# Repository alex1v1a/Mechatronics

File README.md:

# Mechatronics
Progress of Mechatronics 282 778

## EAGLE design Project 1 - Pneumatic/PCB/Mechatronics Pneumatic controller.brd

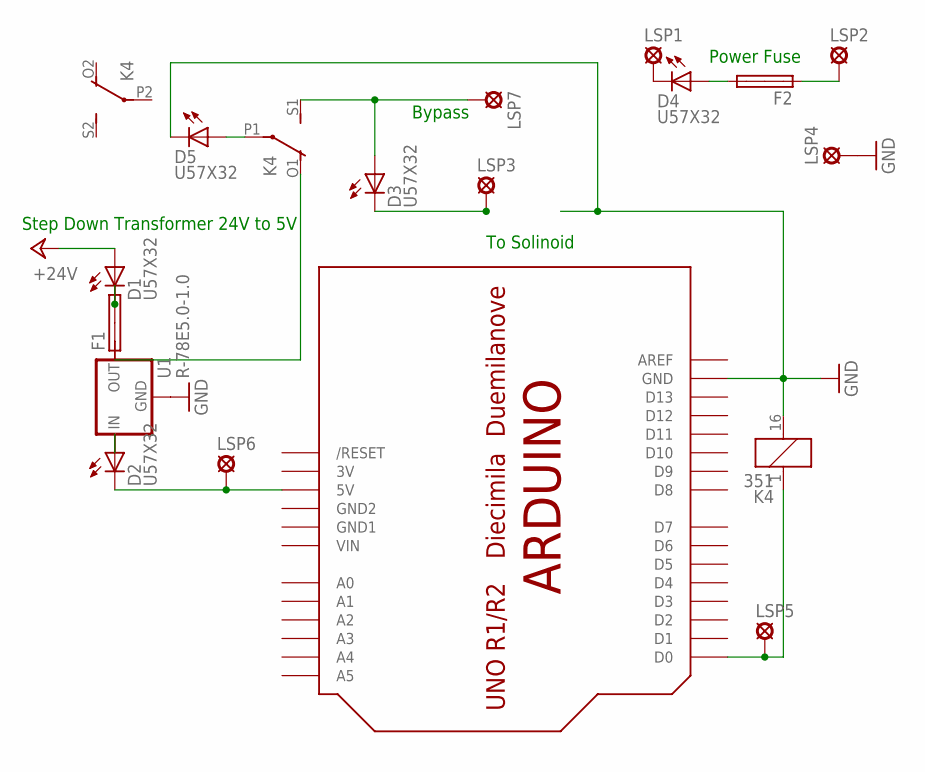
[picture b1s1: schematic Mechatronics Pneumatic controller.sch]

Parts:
D1, D2, D3, D4, D5: U57X32
F1, F2: SHK20L
K4: 351
LSP1, LSP2, LSP3, LSP4, LSP5, LSP6, LSP7: LSP10
U1: R-78E5.0-1.0; DC-DC_CONVERTER_78XX
U$1: ARDUINOUNO; ARDUINO

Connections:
3V: U$1.3V
5VSOURCE: D2.K (C), LSP6.MP, U$1.5V
+24V: D1.A
GND: D5.K (C), K4.16 (2), LSP4.MP, U1.GND, U$1.GND
GND1: U$1.GND1
GND2: U$1.GND2
unnamed: D1.K (C), F1.2A, F1.2B
unnamed: F1.1B, U1.VOUT (OUT)
unnamed: D2.A, U1.VIN (IN)
unnamed: K4.1, LSP5.MP, U$1.D0
unnamed: D3.A, K4.S1 (S), LSP7.MP
unnamed: D3.K (C), LSP3.MP
unnamed: D4.A, F2.2A
unnamed: F2.1A, LSP2.MP
unnamed: D4.K (C), LSP1.MP
unnamed: D5.A, K4.P1
SOLINOID: F1.1A, K4.O1 (O)
VIN: U$1.VIN

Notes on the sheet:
Step Down Transformer 24V to 5V
To Solinoid
Power Fuse
Bypass

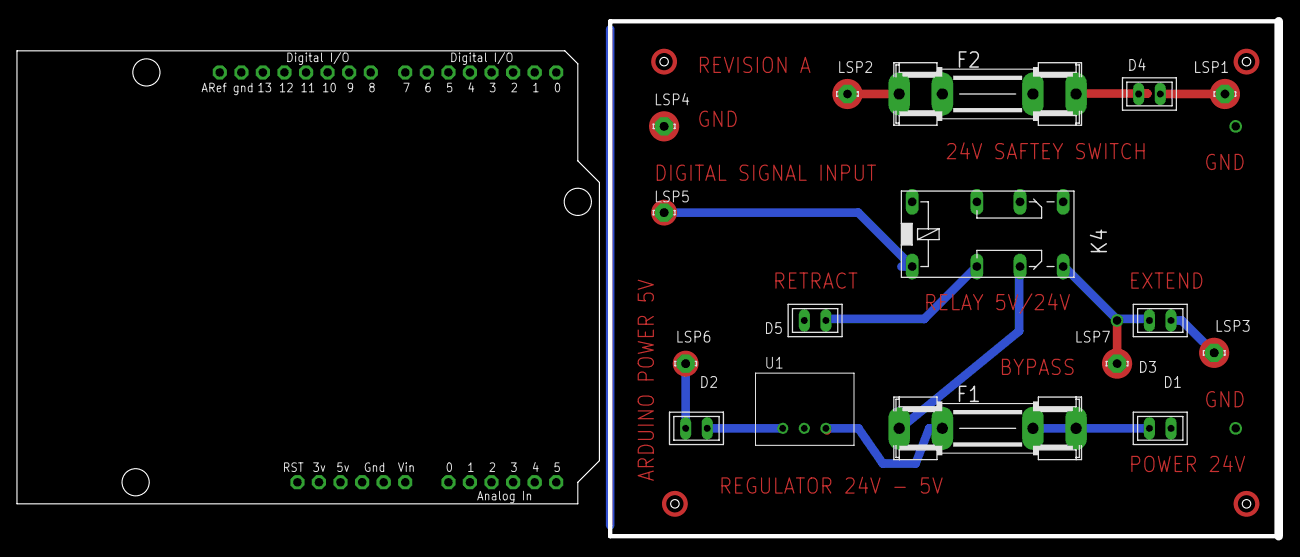
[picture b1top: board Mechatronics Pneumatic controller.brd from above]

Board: 2 copper layers, 148.1 x 60.6 mm, 17 parts (0 on the bottom side), 13 nets.

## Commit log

2017-03-30 Initial upload
    My program files 1-4 and start of latex report
2017-03-30 Project update - Latex
2017-03-30 Finalisation and last edits
    Submit project to stream
2017-04-11 Festo Update formatting A4 paper
2017-05-26 Pneumatic Project
2017-05-30 Laser Project 1 Complete
2017-05-31 Pneumatic Progress
2017-06-03 Pneumatic Schematic and Board finished PCB
2017-06-03 Report start
2017-06-03 Report Progress
2017-06-04 85% complete report
2017-06-08 start programming
2017-06-08 programming

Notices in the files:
parts and their libraries:
SparkFun-IC-Power: Licensing: Creative Commons ShareAlike 4.0 International - https://creativecommons.org/licenses/by-sa/4.0
